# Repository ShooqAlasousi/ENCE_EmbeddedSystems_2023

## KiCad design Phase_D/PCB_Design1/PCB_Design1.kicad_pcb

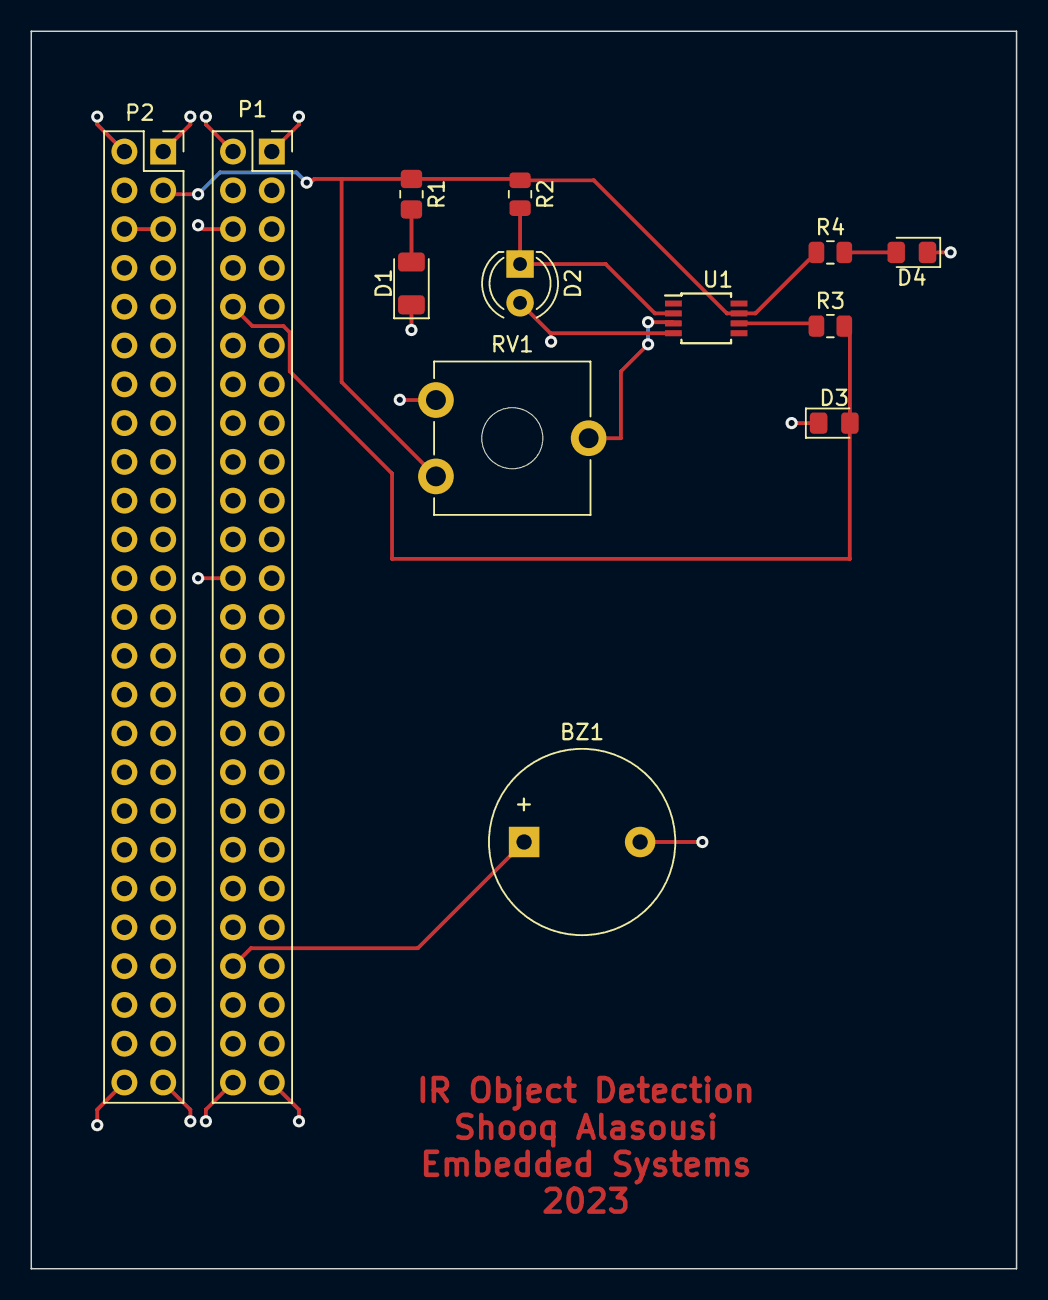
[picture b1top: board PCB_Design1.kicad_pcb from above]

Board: 2 copper layers, 64.5 x 81.0 mm, 13 parts (0 on the bottom side), 10 nets.

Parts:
BZ1: Buzzer; Buzzer_12x9.5RM7.6
D1: IR; LED_1206_3216Metric
D2: D_Photo; LED_D4.0mm
D3, D4: LED; LED_0805_2012Metric_Pad1.15x1.40mm_HandSolder
P1: Discovery Board Conn 1; PinSocket_2x25_P2.54mm_Vertical
P2: Discovery Board Conn 2; PinSocket_2x25_P2.54mm_Vertical
R1: 330; R_0805_2012Metric_Pad1.20x1.40mm_HandSolder
R2, R4: 330; R_0805_2012Metric
R3: 100; R_0805_2012Metric
RV1: 10k_Potentiometer; Potentiometer_ACP_CA9-V10_Vertical_Hole
U1: LM741; TSSOP-8_3x3mm_P0.65mm

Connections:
+3V0: P2.5, P2.6
Buzzer: BZ1.1 (-), P1.44
GND: BZ1.2 (+), D1.1 (K), D2.2 (A), D3.1 (K), D4.1 (K), P1.1, P1.2, P1.6, P1.24, P1.49, P1.50, P2.1, P2.2, P2.49, P2.50, RV1.3, U1.4 (V-)
IR_OUTPUT: D3.2 (A), P1.10, R3.2
unnamed: D1.2 (A), R1.2
unnamed: D2.1 (K), R2.2, U1.2 (-)
unnamed: D4.2 (A), R4.2
unnamed: R3.1, U1.6
unnamed: RV1.2, U1.3 (+)
VDD: P2.3, R1.1, R2.1, R4.1, RV1.1, U1.7 (V+)

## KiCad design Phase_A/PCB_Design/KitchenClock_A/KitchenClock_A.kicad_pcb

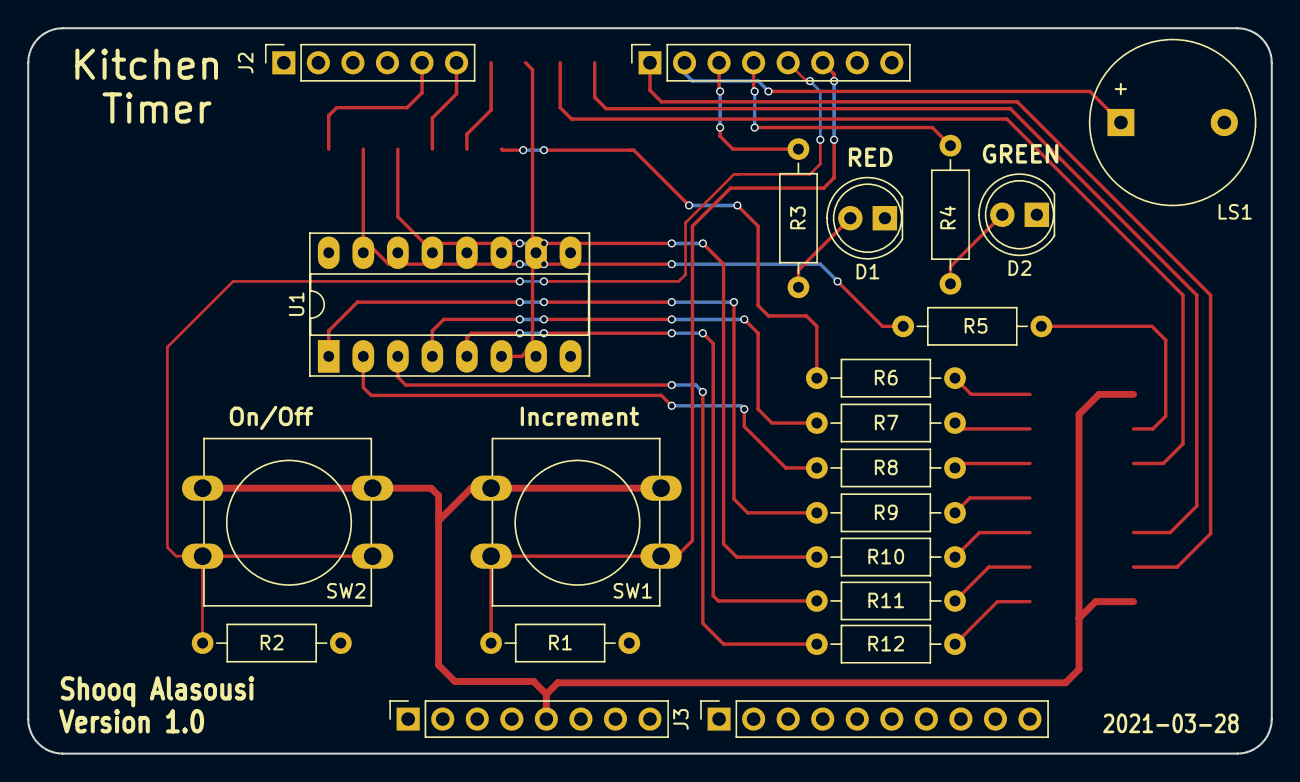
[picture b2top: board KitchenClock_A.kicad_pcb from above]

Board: 2 copper layers, 91.4 x 53.3 mm, 22 parts (0 on the bottom side), 20 nets.

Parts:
D1, D2: LED; LED_D5.0mm
J1: Power; PinSocket_1x08_P2.54mm_Vertical
J2: Analog; PinSocket_1x06_P2.54mm_Vertical
J3: Digital/PWM; PinSocket_1x10_P2.54mm_Vertical
J4: Digital/PWM; PinSocket_1x08_P2.54mm_Vertical
LS1: Speaker; Buzzer_12x9.5RM7.6
R1, R2: 330; R_Axial_DIN0207_L6.3mm_D2.5mm_P10.16mm_Horizontal
R3, R4, R5, R6, R7, R8, R9, R10: 100; R_Axial_DIN0207_L6.3mm_D2.5mm_P10.16mm_Horizontal
R11, R12: 10k; R_Axial_DIN0207_L6.3mm_D2.5mm_P10.16mm_Horizontal
SW1, SW2: SW_Push; SW_PUSH-12mm
U1: 74HC595; DIP-16_W7.62mm_Socket_LongPads

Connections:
+5V: J1.5, SW1.1, SW2.1, U1.10 (~SRCLR), U1.16 (VCC)
Button_1: J4.6, R11.1, SW1.2
Button_2: J4.5, R12.1, SW2.2
Buzzer: J4.2, LS1.1
DS: J3.9, U1.14 (SER)
GND: D1.1 (K), D2.1 (K), J1.6, J1.7, J3.4, LS1.2, R11.2, R12.2, U1.8 (GND), U1.13 (~OE)
GREEN_LED: J4.4, R2.1
unnamed: D1.2 (A), R1.2
unnamed: D2.2 (A), R2.2
RED_LED: J4.3, R1.1
SH_CP: J4.1, U1.11 (SRCLK)
ST_CP: J3.10, U1.12 (RCLK)
a: R3.1, U1.15 (QA)
b: R4.1, U1.1 (QB)
c: R5.1, U1.2 (QC)
d: R6.1, U1.3 (QD)
dp: R10.1, U1.7 (QH)
e: R7.1, U1.4 (QE)
f: R8.1, U1.5 (QF)
g: R9.1, U1.6 (QG)

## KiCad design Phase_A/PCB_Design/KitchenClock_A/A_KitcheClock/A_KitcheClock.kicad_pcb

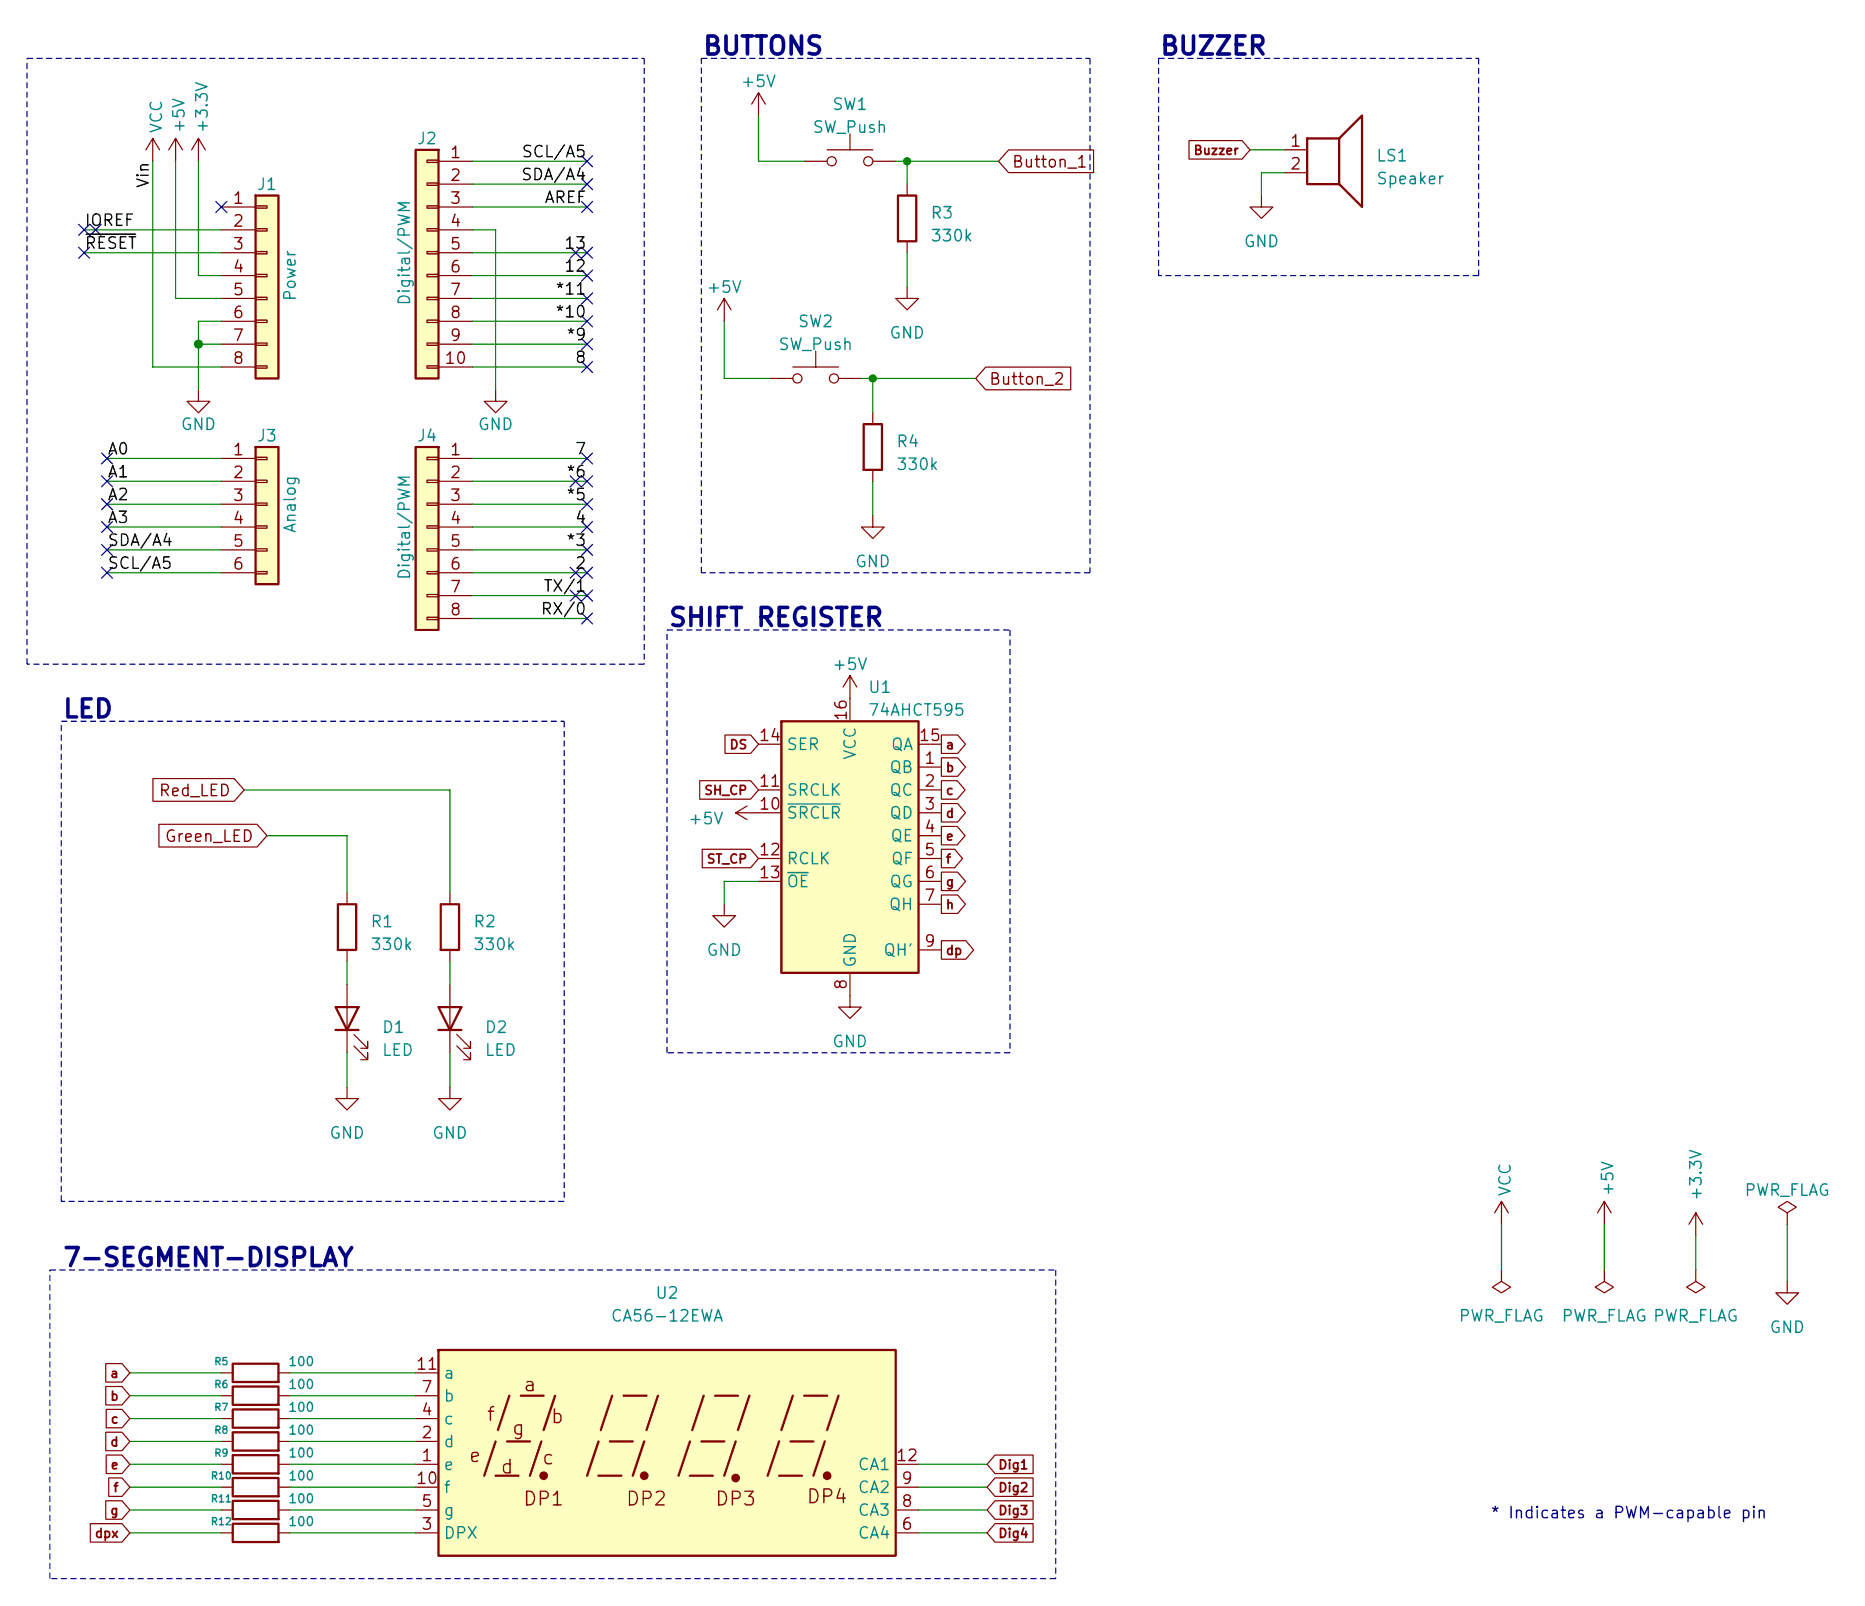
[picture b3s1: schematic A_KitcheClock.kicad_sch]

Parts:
D1, D2: LED; LED_D3.0mm_Clear
J1: Power; PinSocket_1x08_P2.54mm_Vertical
J2: Digital/PWM; PinSocket_1x10_P2.54mm_Vertical
J3: Analog; PinSocket_1x06_P2.54mm_Vertical
J4: Digital/PWM; PinSocket_1x08_P2.54mm_Vertical
LS1: Speaker; Buzzer_12x9.5RM7.6
R1: 330k; R_Axial_DIN0207_L6.3mm_D2.5mm_P10.16mm_Horizontal
R2, R3, R4: 330k; R_Axial_DIN0207_L6.3mm_D2.5mm_P15.24mm_Horizontal
R5, R6, R7, R8, R9, R10, R11, R12: 100; R_Axial_DIN0207_L6.3mm_D2.5mm_P15.24mm_Horizontal
SW1, SW2: SW_Push; SW_PUSH_6mm
U1: 74AHCT595
U2: CA56-12EWA

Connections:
+3V3: J1.4
+5V: J1.5, SW1.1, SW2.1, U1.10 (~SRCLR), U1.16 (VCC)
/2: J4.6
/4: J4.4
/7: J4.1
/8: J2.10
/12: J2.6
/13: J2.5
/*3: J4.5
/*5: J4.3
/*6: J4.2
/*9: J2.9
/*10: J2.8
/*11: J2.7
/A0: J3.1
/A1: J3.2
/A2: J3.3
/A3: J3.4
/AREF: J2.3
/IOREF: J1.2
/RX/0: J4.8
/SCL/A5: J2.1, J3.6
/SDA/A4: J2.2, J3.5
/TX/1: J4.7
/~RESET: J1.3
Button_1: R3.1, SW1.2
Button_2: R4.1, SW2.2
Buzzer: LS1.1
Dig1: U2.12 (CA1)
Dig2: U2.9 (CA2)
Dig3: U2.8 (CA3)
Dig4: U2.6 (CA4)
GND: D1.1 (K), D2.1 (K), J1.6, J1.7, J2.4, LS1.2, R3.2, R4.2, U1.8 (GND), U1.13 (~OE)
Green_LED: R1.1
unnamed: D1.2 (A), R1.2
unnamed: D2.2 (A), R2.2
unnamed: R12.2, U2.3 (DPX)
unnamed: R5.2, U2.11 (a)
unnamed: R6.2, U2.7 (b)
unnamed: R7.2, U2.4 (c)
unnamed: R8.2, U2.2 (d)
unnamed: R9.2, U2.1 (e)
unnamed: R10.2, U2.10 (f)
unnamed: R11.2, U2.5 (g)
Red_LED: R2.1
VCC: J1.8
a: R5.1, U1.15 (QA)
b: R6.1, U1.1 (QB)
c: R7.1, U1.2 (QC)
d: R8.1, U1.3 (QD)
dpx: R12.1
e: R9.1, U1.4 (QE)
f: R10.1, U1.5 (QF)
g: R11.1, U1.6 (QG)

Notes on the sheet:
BUTTONS
BUZZER
LED
* Indicates a PWM-capable pin
7-SEGMENT-DISPLAY
SHIFT REGISTER

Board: 2 copper layers, 22 parts (0 on the bottom side), 16 nets, no tracks yet.

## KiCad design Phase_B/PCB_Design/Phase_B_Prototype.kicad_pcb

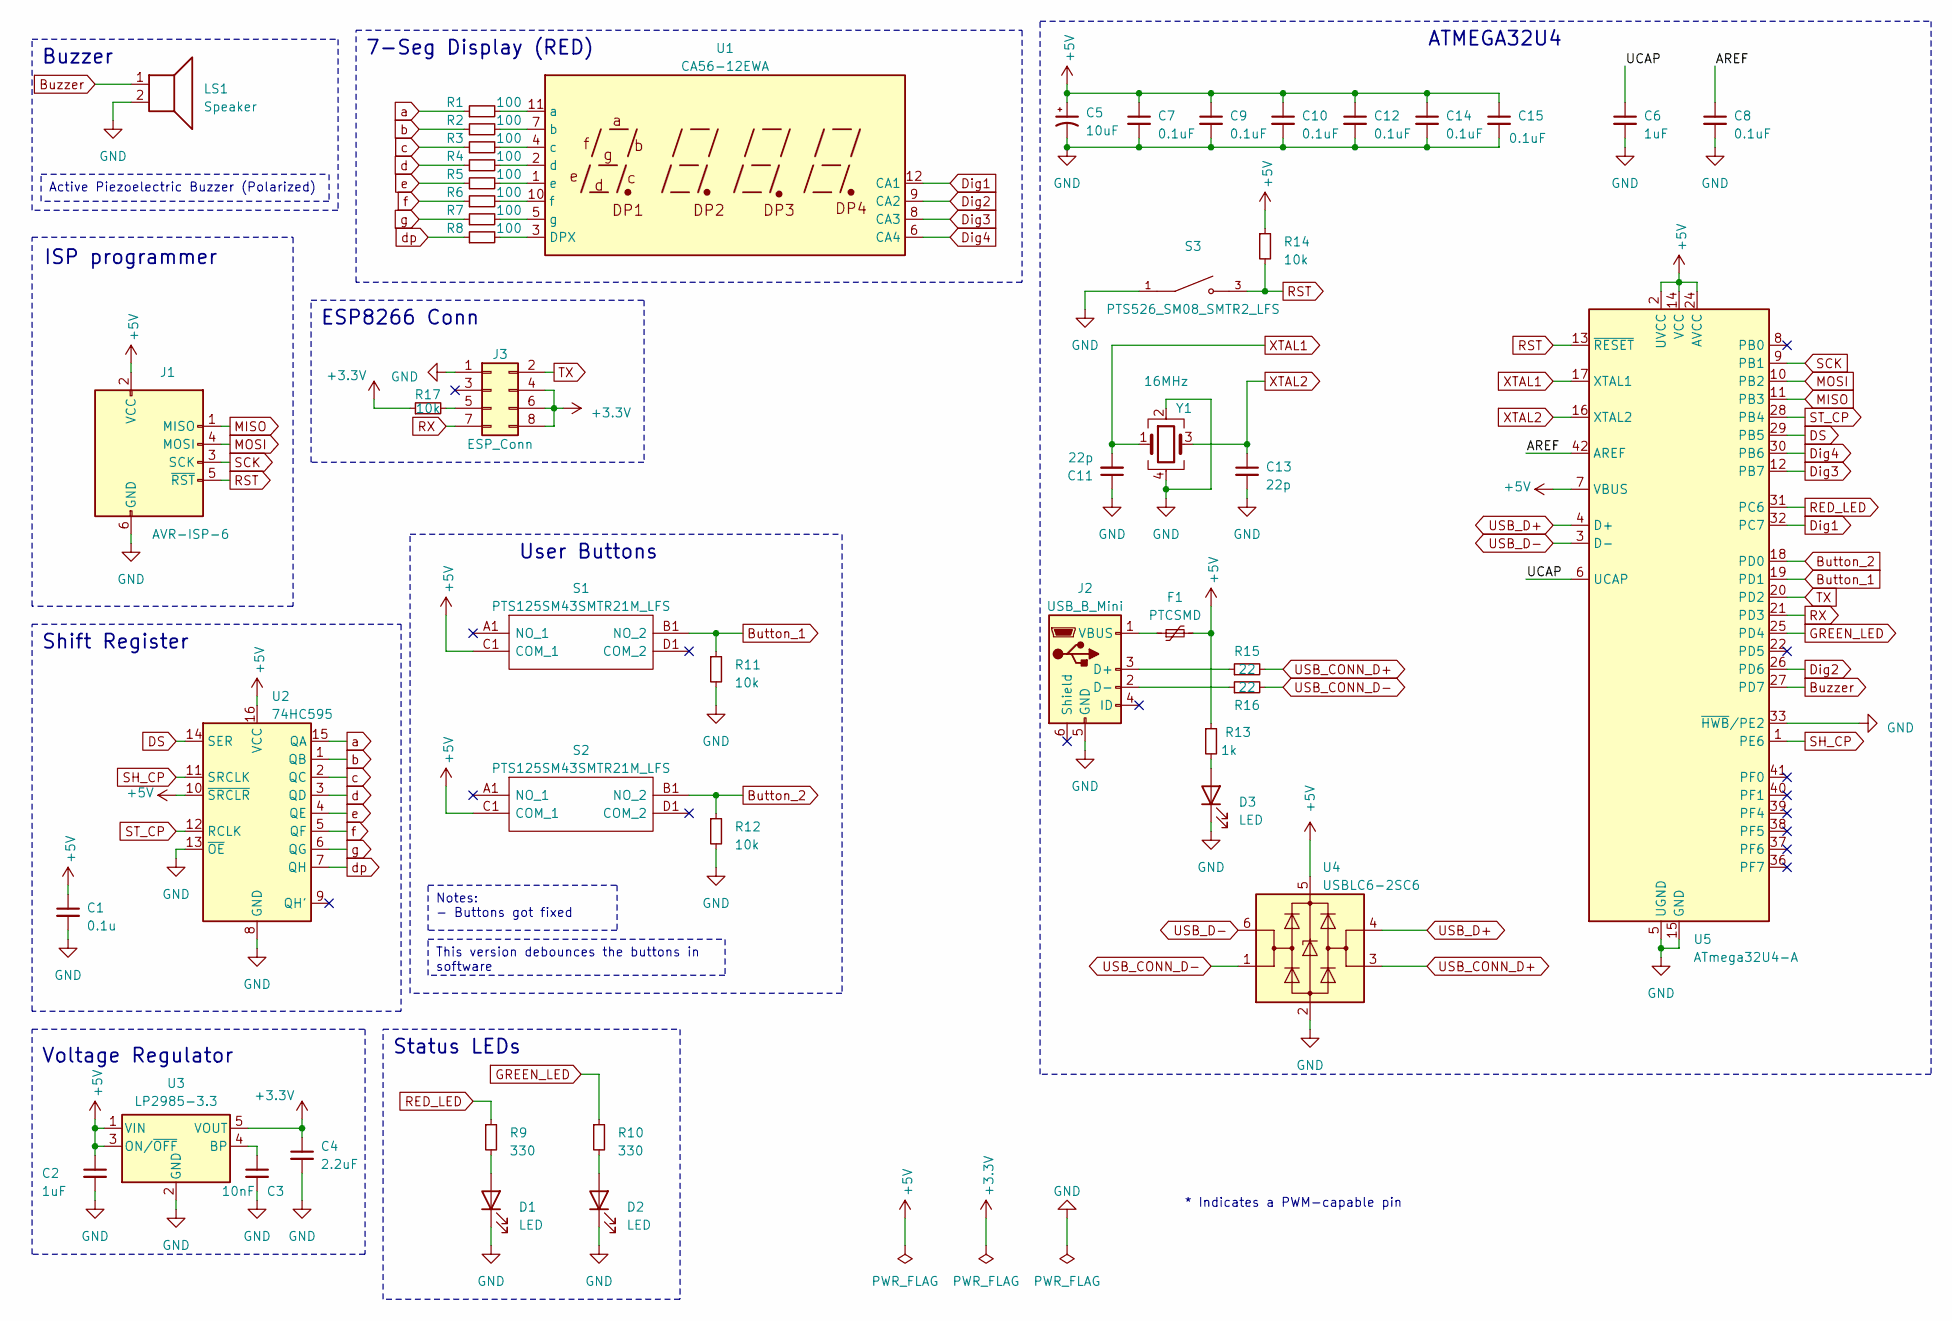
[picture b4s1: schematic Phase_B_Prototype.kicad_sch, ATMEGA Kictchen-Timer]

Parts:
C1: 0.1u; C_0603_1608Metric
C2, C6: 1uF; C_0603_1608Metric
C3: 10nF; C_0603_1608Metric
C4: 2.2uF; C_0603_1608Metric
C5: 10uF; C_0805_2012Metric
C7, C8, C9, C10, C12, C14, C15: 0.1uF; C_0603_1608Metric
C11, C13: 22p; C_0603_1608Metric
D1, D2, D3: LED; LED_0805_2012Metric
F1: PTCSMD; Fuse_1812_4532Metric
J1: AVR-ISP-6; PinSocket_2x03_P2.54mm_Vertical
J2: USB_B_Mini; USB_Mini-B_Lumberg_2486_01_Horizontal
J3: ESP_Conn; PinSocket_2x04_P2.54mm_Vertical
LS1: Speaker; Buzzer_12x9.5RM7.6
R1, R2, R3, R4, R5, R6, R7, R8: 100; R_0805_2012Metric
R9, R10: 330; R_0805_2012Metric
R11, R12: 10k; R_0805_2012Metric
R13: 1k; R_0603_1608Metric
R14, R17: 10k; R_0603_1608Metric
R15, R16: 22; R_0603_1608Metric
S1, S2: PTS125SM43SMTR21M_LFS; PTS125_SMD_Button; Manufacturer_Part_Number PTS125SM43SMTR21M LFS; Mouser Part Number 611-PTS125S43SMTRLFS
S3: PTS526_SM08_SMTR2_LFS; PTS526_SMD_Button; PARTREV 20 mar 19
U1: CA56-12EWA
U2: 74HC595; TSSOP-16_4.4x5mm_P0.65mm
U3: LP2985-3.3; SOT-23-5
U4: USBLC6-2SC6; SOT-23-6
U5: ATmega32U4-A; TQFP-44_10x10mm_P0.8mm
Y1: 16MHz; Crystal_SMD_Abracon_ABM8G-4Pin_3.2x2.5mm

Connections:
+3.3V: C4.1, J3.4, J3.6, J3.8, R17.1, U3.5 (VOUT)
+5V: C1.1, C2.1, C5.1, C7.1, C9.1, C10.1, C12.1, C14.1, C15.1, F1.2, J1.2 (VCC), R13.1, R14.1, S1.C1 (COM_1), S2.C1 (COM_1), U2.10 (~SRCLR), U2.16 (VCC), U3.1 (VIN), U3.3 (ON/~OFF), U4.5 (VBUS), U5.2 (UVCC), U5.7 (VBUS), U5.14 (VCC), U5.24 (AVCC), U5.34 (VCC), U5.44 (AVCC)
/AREF: C8.1, U5.42 (AREF)
/UCAP: C6.1, U5.6 (UCAP)
Button_1: R11.1, S1.B1 (NO_2), U5.19 (PD1)
Button_2: R12.1, S2.B1 (NO_2), U5.18 (PD0)
Buzzer: LS1.1, U5.27 (PD7)
DS: U2.14 (SER), U5.29 (PB5)
Dig1: U1.12 (CA1), U5.32 (PC7)
Dig2: U1.9 (CA2), U5.26 (PD6)
Dig3: U1.8 (CA3), U5.12 (PB7)
Dig4: U1.6 (CA4), U5.30 (PB6)
GND: C1.2, C2.2, C3.2, C4.2, C5.2, C6.2, C7.2, C8.2, C9.2, C10.2, C11.1, C12.2, C13.2, C14.2, C15.2, D1.1 (K), D2.1 (K), D3.1 (K), J1.6 (GND), J2.5 (GND), J3.1, LS1.2, R11.2, R12.2, S3.1, U2.8 (GND), U2.13 (~OE), U3.2 (GND), U4.2 (GND), U5.5 (UGND), U5.15 (GND), U5.23 (GND), U5.33 (~HWB/PE2), U5.35 (GND), U5.43 (GND), Y1.2, Y1.4
GREEN_LED: R10.1, U5.25 (PD4)
MISO: J1.1 (MISO), U5.11 (PB3)
MOSI: J1.4 (MOSI), U5.10 (PB2)
unnamed: D1.2 (A), R9.2
unnamed: D2.2 (A), R10.2
unnamed: D3.2 (A), R13.2
unnamed: J2.3 (D+), R15.1
unnamed: J2.2 (D-), R16.1
unnamed: F1.1, J2.1 (VBUS)
unnamed: J3.5, R17.2
unnamed: R8.2, U1.3 (DPX)
unnamed: R1.2, U1.11 (a)
unnamed: R2.2, U1.7 (b)
unnamed: R3.2, U1.4 (c)
unnamed: R4.2, U1.2 (d)
unnamed: R5.2, U1.1 (e)
unnamed: R6.2, U1.10 (f)
unnamed: R7.2, U1.5 (g)
unnamed: C3.1, U3.4 (BP)
RED_LED: R9.1, U5.31 (PC6)
RST: J1.5 (~RST), R14.2, S3.3, U5.13 (~RESET)
RX: J3.7, U5.21 (PD3)
SCK: J1.3 (SCK), U5.9 (PB1)
SH_CP: U2.11 (SRCLK), U5.1 (PE6)
ST_CP: U2.12 (RCLK), U5.28 (PB4)
TX: J3.2, U5.20 (PD2)
USB_CONN_D+: R15.2, U4.3 (I/O2)
USB_CONN_D-: R16.2, U4.1 (I/O1)
USB_D+: U4.4 (I/O2), U5.4 (D+)
USB_D-: U4.6 (I/O1), U5.3 (D-)
XTAL1: C11.2, U5.17 (XTAL1), Y1.1
XTAL2: C13.1, U5.16 (XTAL2), Y1.3
a: R1.1, U2.15 (QA)
b: R2.1, U2.1 (QB)
c: R3.1, U2.2 (QC)
d: R4.1, U2.3 (QD)
dp: R8.1, U2.7 (QH)
e: R5.1, U2.4 (QE)
f: R6.1, U2.5 (QF)
g: R7.1, U2.6 (QG)

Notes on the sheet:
Notes: - Buttons got fixed
Active Piezoelectric Buzzer (Polarized)
This version debounces the buttons in software
ISP programmer
Buzzer
7-Seg Display (RED)
ATMEGA32U4
Voltage Regulator
User Buttons
Shift Register
ESP8266 Conn
* Indicates a PWM-capable pin
Status LEDs

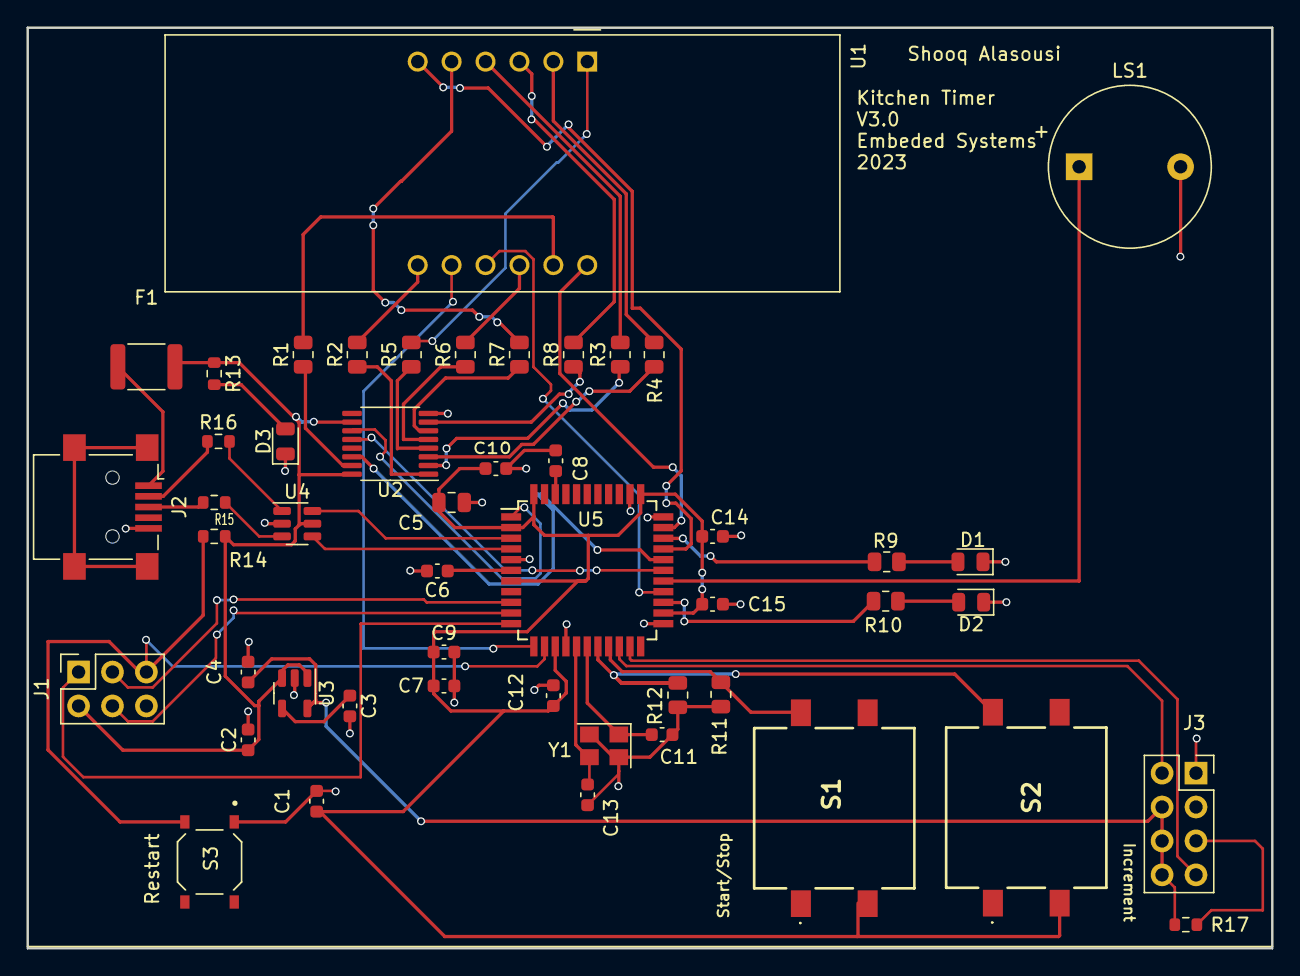
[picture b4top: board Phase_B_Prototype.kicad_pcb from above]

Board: 2 copper layers, 93.2 x 69.0 mm, 49 parts (0 on the bottom side), 53 nets.
